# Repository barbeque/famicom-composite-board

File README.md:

# Famicom Composite Mod
A composite video and audio modification meant for original red-and-white Nintendo Famicoms.

Famicoms came from the factory with RF output, which is normally fine, but Japanese television channel frequencies don't line up with North American ones. Even though both television standards are NTSC, it can be annoying to find a VCR or television set capable of tuning into those channels.

This modification bypasses the RF modulator entirely, and taps into the composite video output coming off of the PPU (Picture Processing Unit; the video chip) of the Famicom. It then sends the video through a voltage divider to step it down to normal composite video voltage levels, and passes through a common Texas Instruments video amplifier IC.

This modification was developed as part of a Leaded Solder blog project, which you can read about in the following entries:
 - [Adding composite video to a Famicom](https://www.leadedsolder.com/2020/12/17/famicom-composite-mod-v1.html)
 - [Revenge of the Famicom composite video mod](https://www.leadedsolder.com/2021/06/15/famicom-composite-mod-v2.html)

If you like the projects, please [consider becoming a patron](https://www.patreon.com/leadedsolder). Your membership helps pay for the prototyping and development of more modifications just like this.

## Installation
TODO

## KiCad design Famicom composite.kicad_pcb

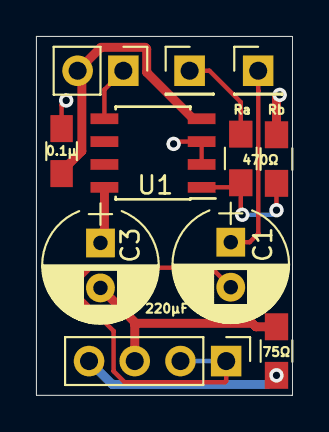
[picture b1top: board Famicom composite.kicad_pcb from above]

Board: 2 copper layers, 14.2 x 19.9 mm, 11 parts (0 on the bottom side), 8 nets.

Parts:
C1: 220µF; CP_Radial_D6.3mm_P2.50mm
C2: 0.1µF; C_0805_HandSoldering
C3: 330µF; CP_Radial_D6.3mm_P2.50mm
J1: PPU_Pin21; Pin_Header_Straight_1x01_Pitch2.54mm
J2: Conn_01x02; Pin_Header_Straight_1x02_Pitch2.54mm
J3: Audio_In; Pin_Header_Straight_1x01_Pitch2.54mm
J4: Conn_01x04_Female; Pin_Header_Straight_1x04_Pitch2.54mm
R1, R3: 470Ω; R_0805_HandSoldering
R2: 75Ω; R_0805_HandSoldering
U1: THS7314; SOIC-8_3.9x4.9mm_Pitch1.27mm

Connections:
+5V: C2.1, J2.2, U1.4
/Half_Vpp: R1.2, R3.1, U1.1
/Vid_Out: C3.2, J4.3, R2.2
GND: C2.2, J2.1, J4.4, R2.1, R3.2, U1.2, U1.3, U1.5
unnamed: C1.1, J3.1
unnamed: C1.2, J4.1, J4.2
unnamed: C3.1, U1.8
unnamed: J1.1, R1.1

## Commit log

2020-06-05 v0.1 - dunno if this will work
2020-06-08 Twin Famicom design
2020-06-08 THS7314 analogue video amp version
2020-07-17 v0.3 - 75ohm attenuation, video filter cap
2020-07-23 add input-side cap, ground other inputs
2020-07-31 Add 3M input pullup pad
2020-08-01 Voltage divider variant
2020-08-01 Pushed to PCB
2021-04-29 Label the dividers
2021-08-29 75ohm pulldown
2021-09-11 75-ohm series resistor
2021-09-11 BBCBC version sent to Osh
2021-12-13 Clean up schematic
2024-03-19 Update to KiCad 7
2024-03-19 Add footprint cache back
2024-03-19 Release v0.6
2024-03-20 Basic README
2024-03-20 Add ko-fi link
